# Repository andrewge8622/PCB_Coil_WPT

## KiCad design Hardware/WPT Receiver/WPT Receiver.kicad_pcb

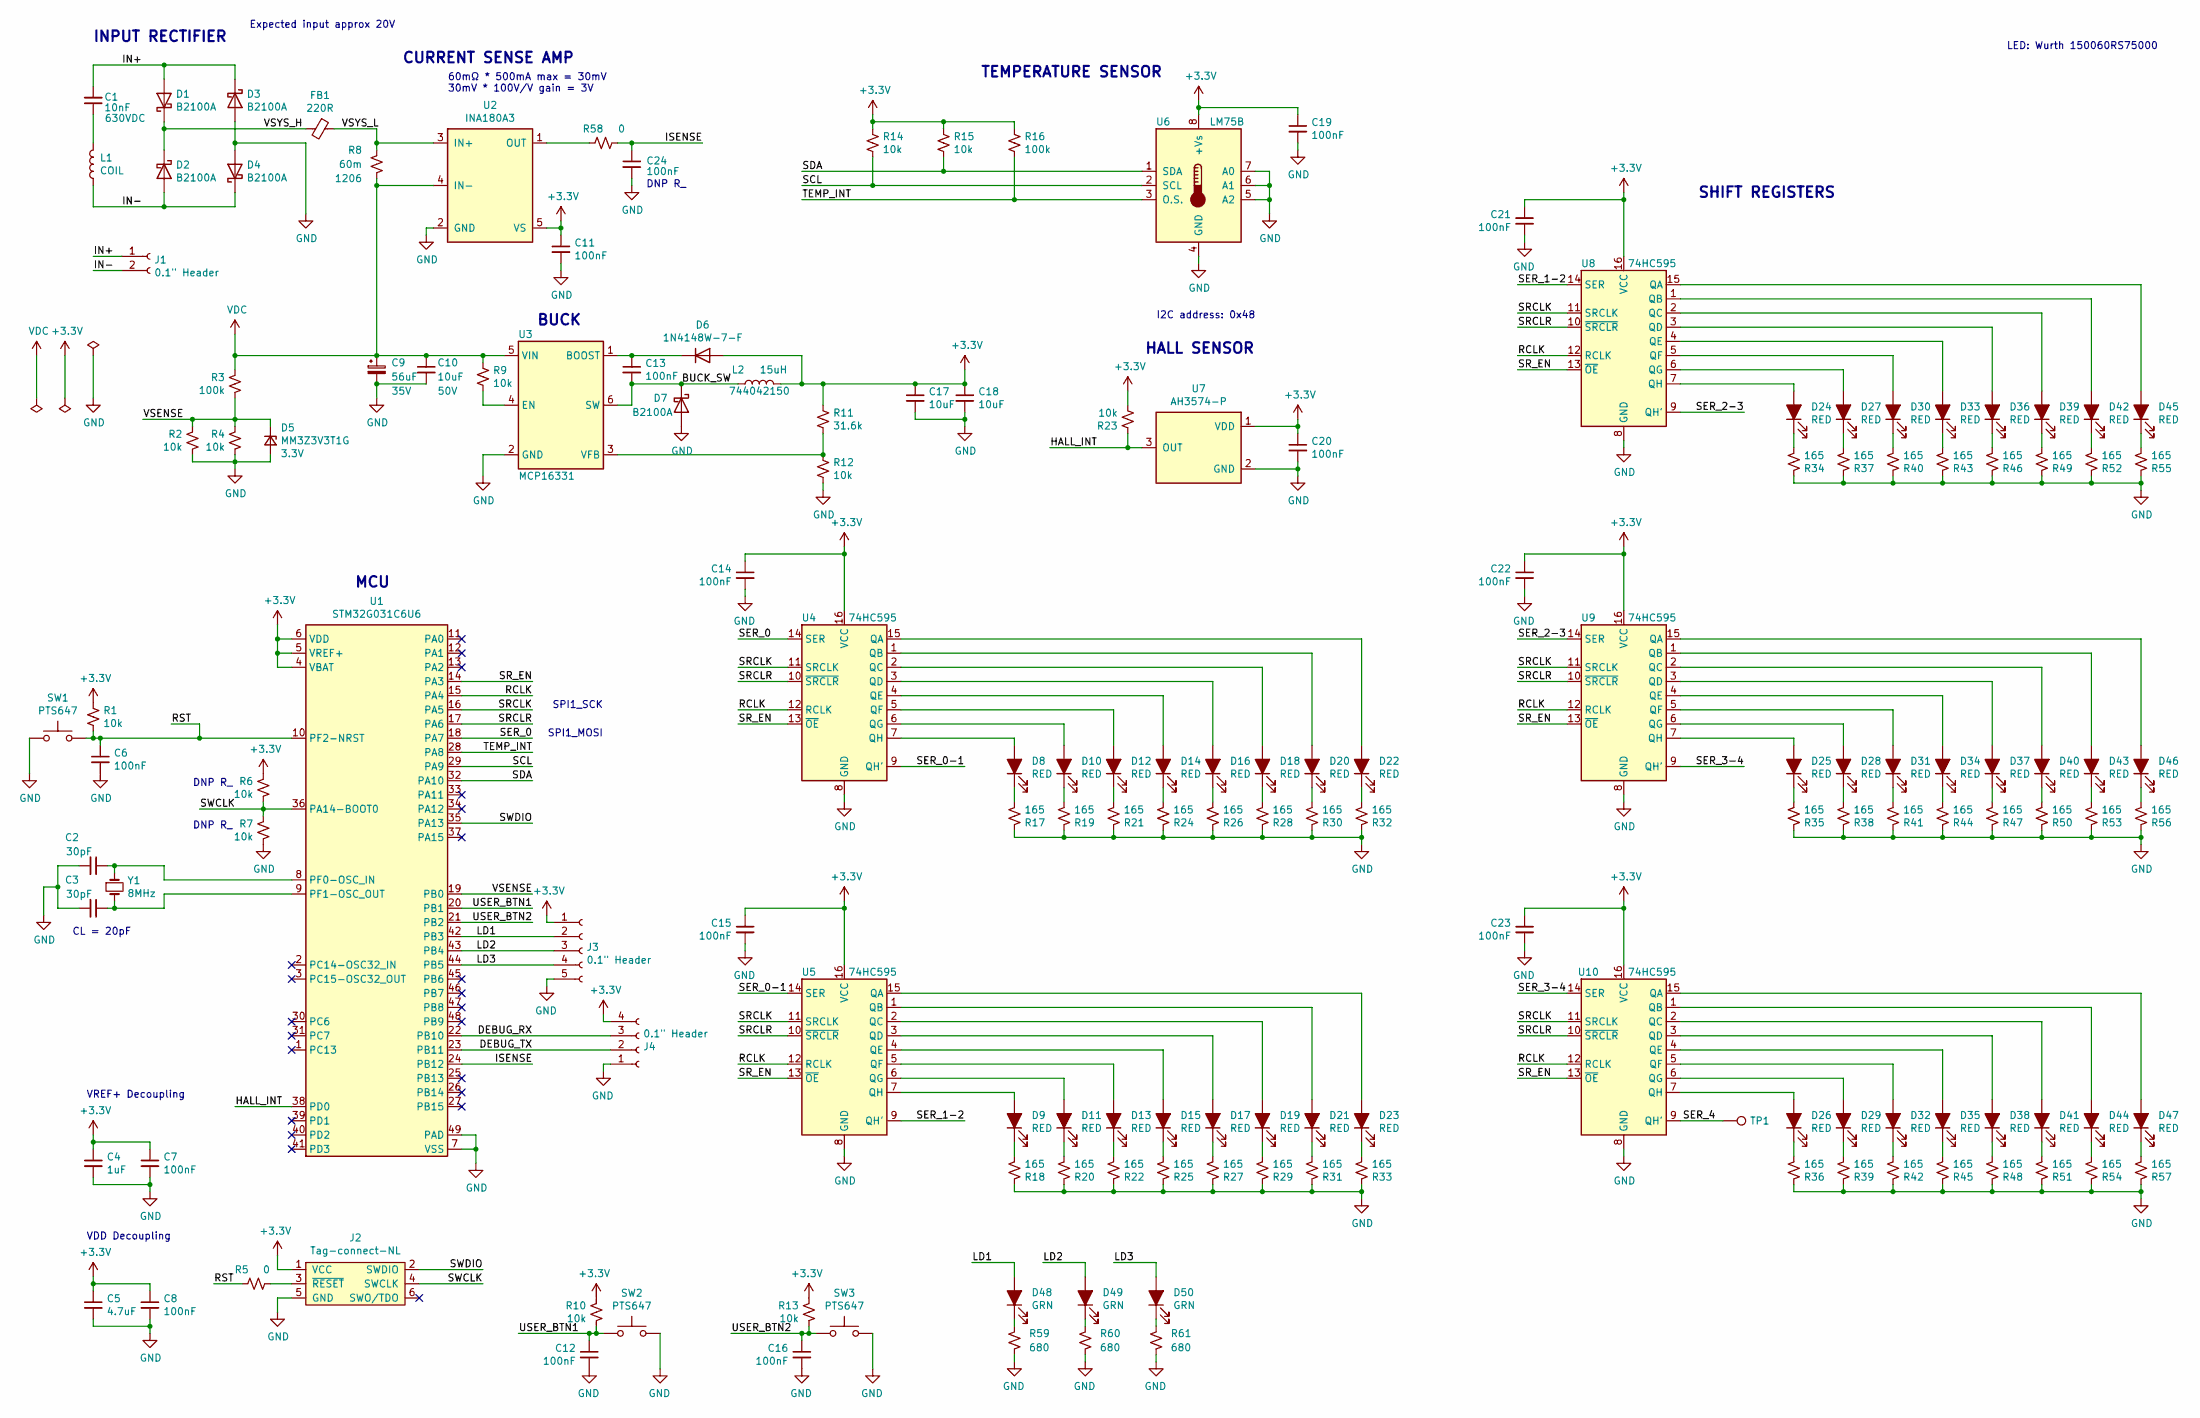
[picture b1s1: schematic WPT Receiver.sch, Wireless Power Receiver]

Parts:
C1: 10nF; C_Rect_L7.2mm_W8.5mm_P5.00mm_FKP2_FKP2_MKS2_MKP2; Voltage 630VDC
C2, C3: 30pF; C_0402_1005Metric
C4: 1uF; C_0603_1608Metric
C5: 4.7uF; C_0603_1608Metric
C6, C7, C8, C11, C12, C13, C14, C15, C16, C19, C20, C21, C22, C23, C24: 100nF; C_0402_1005Metric
C9: 56uF; CP_Elec_10x10; MPN EMVA630ADA560MJA0G
C10, C17, C18: 10uF; C_0603_1608Metric
D1, D2, D3, D4, D7: B2100A; D_SMA
D5: MM3Z3V3T1G; D_SOD-323; Voltage 3.3V
D6: 1N4148W-7-F; D_SOD-123
D8, D9, D10, D11, D12, D13, D14, D15, D16, D17, D18, D19, D20, D21, D22, D23, D24, D25, D26, D27, D28, D29, D30, D31, D32, D33, D34, D35, D36, D37, D38, D39, D40, D41, D42, D43, D44, D45, D46, D47: RED; LED_0603_1608Metric_Castellated
D48, D49, D50: GRN; LED_0603_1608Metric_Castellated; MPN 150060VS75000
FB1: 220R; L_0603_1608Metric
J1: 0.1\" Header; PinHeader_1x02_P2.54mm_Vertical
J2: Tag-connect-NL; TC2030-IDC-NL-FP
J3: 0.1\" Header; PinHeader_1x05_P2.54mm_Vertical
J4: 0.1\" Header; PinHeader_1x04_P2.54mm_Vertical
L1: COIL; PinHeader_2x01_P2.54mm_Vertical
L2: 15uH; 744042150; MPN 744042150
R1, R2, R4, R6, R7, R9, R10, R12, R13, R14, R15, R23: 10k; R_0603_1608Metric
R3, R16: 100k; R_0603_1608Metric
R5, R58: 0; R_0603_1608Metric
R8: 60m; R_1206_3216Metric
R11: 31.6k; R_0603_1608Metric
R17, R18, R19, R20, R21, R22, R24, R25, R26, R27, R28, R29, R30, R31, R32, R33, R34, R35, R36, R37, R38, R39, R40, R41, R42, R43, R44, R45, R46, R47, R48, R49, R50, R51, R52, R53, R54, R55, R56, R57: 165; R_0603_1608Metric
R59, R60, R61: 680; R_0603_1608Metric
SW1, SW2, SW3: PTS647
TP1: TestPoint; TestPoint_Pad_2.5x2.5mm
U1: STM32G031C6U6; QFN-48-1EP_7x7mm_P0.5mm_EP5.6x5.6mm
U2: INA180A3; SOT-23-5
U3: MCP16331; SOT-23-6
U4, U5, U8, U9, U10: 74HC595; SOIC-16_3.9x9.9mm_P1.27mm
U6: LM75B; SOIC-8_3.9x4.9mm_P1.27mm
U7: AH3574-P; TO-92Flat
Y1: 8MHz; Crystal_SMD_5032-2Pin_5.0x3.2mm

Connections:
+3V3: C4.1, C5.1, C7.1, C8.1, C11.1, C14.1, C15.1, C17.1, C18.1, C19.1, C20.1, C21.1, C22.1, C23.1, D6.2 (A), J2.1 (VCC), J3.1, J4.4, L2.2, R1.1, R6.2, R10.1, R11.1, R13.1, R14.1, R15.1, R16.1, R23.2, U1.4 (VBAT), U1.5 (VREF+), U1.6 (VDD), U2.5 (VS), U4.16 (VCC), U5.16 (VCC), U6.8 (+Vs), U7.1 (VDD), U8.16 (VCC), U9.16 (VCC), U10.16 (VCC)
/BUCK_SW: C13.2, D7.1 (K), L2.1, U3.6 (SW)
/DEBUG_RX: J4.3, U1.22 (PB10)
/DEBUG_TX: J4.2, U1.23 (PB11)
/HALL_INT: R23.1, U1.38 (PD0), U7.3 (OUT)
/IN+: C1.2, D1.2 (A), D3.1 (K), J1.1
/IN-: D2.2 (A), D4.1 (K), J1.2, L1.1
/ISENSE: C24.1, R58.1, U1.24 (PB12)
/LD1: D48.2 (A), J3.2, U1.42 (PB3)
/LD2: D49.2 (A), J3.3, U1.43 (PB4)
/LD3: D50.2 (A), J3.4, U1.44 (PB5)
/RCLK: U1.15 (PA4), U4.12 (RCLK), U5.12 (RCLK), U8.12 (RCLK), U9.12 (RCLK), U10.12 (RCLK)
/RST: C6.1, R1.2, R5.1, SW1.2, U1.10 (PF2-NRST)
/SCL: R14.2, U1.29 (PA9), U6.2 (SCL)
/SDA: R15.2, U1.32 (PA10), U6.1 (SDA)
/SER_0: U1.18 (PA7), U4.14 (SER)
/SER_0-1: U4.9 (QH'), U5.14 (SER)
/SER_1-2: U5.9 (QH'), U8.14 (SER)
/SER_2-3: U8.9 (QH'), U9.14 (SER)
/SER_3-4: U9.9 (QH'), U10.14 (SER)
/SER_4: TP1.1, U10.9 (QH')
/SRCLK: U1.16 (PA5), U4.11 (SRCLK), U5.11 (SRCLK), U8.11 (SRCLK), U9.11 (SRCLK), U10.11 (SRCLK)
/SRCLR: U1.17 (PA6), U4.10 (~SRCLR), U5.10 (~SRCLR), U8.10 (~SRCLR), U9.10 (~SRCLR), U10.10 (~SRCLR)
/SR_EN: U1.14 (PA3), U4.13 (~OE), U5.13 (~OE), U8.13 (~OE), U9.13 (~OE), U10.13 (~OE)
/SWCLK: J2.4 (SWCLK), R6.1, R7.2, U1.36 (PA14-BOOT0)
/SWDIO: J2.2 (SWDIO), U1.35 (PA13)
/TEMP_INT: R16.2, U1.28 (PA8), U6.3 (O.S.)
/USER_BTN1: C12.1, R10.2, SW2.2, U1.20 (PB1)
/USER_BTN2: C16.1, R13.2, SW3.2, U1.21 (PB2)
/VSENSE: D5.1 (K), R2.1, R3.2, R4.1, U1.19 (PB0)
/VSYS_H: D1.1 (K), D2.1 (K), FB1.2
/VSYS_L: FB1.1, R8.1, U2.3 (IN+)
GND: C2.2, C3.2, C4.2, C5.2, C6.2, C7.2, C8.2, C9.2, C10.2, C11.2, C12.2, C14.2, C15.2, C16.2, C17.2, C18.2, C19.2, C20.2, C21.2, C22.2, C23.2, C24.2, D3.2 (A), D4.2 (A), D5.2 (A), D7.2 (A), J2.5 (GND), J3.5, J4.1, R2.2, R4.2, R7.1, R12.2, R17.2, R18.2, R19.2, R20.2, R21.2, R22.2, R24.2, R25.2, R26.2, R27.2, R28.2, R29.2, R30.2, R31.2, R32.2, R33.2, R34.2, R35.2, R36.2, R37.2, R38.2, R39.2, R40.2, R41.2, R42.2, R43.2, R44.2, R45.2, R46.2, R47.2, R48.2, R49.2, R50.2, R51.2, R52.2, R53.2, R54.2, R55.2, R56.2, R57.2, R59.2, R60.2, R61.2, SW1.1, SW2.1, SW3.1, U1.7 (VSS), U1.49 (PAD), U2.2 (GND), U3.2 (GND), U4.8 (GND), U5.8 (GND), U6.4 (GND), U6.5 (A2), U6.6 (A1), U6.7 (A0), U7.2 (GND), U8.8 (GND), U9.8 (GND), U10.8 (GND)
unnamed: C1.1, L1.2
unnamed: C2.1, U1.8 (PF0-OSC_IN), Y1.1
unnamed: C3.1, U1.9 (PF1-OSC_OUT), Y1.2
unnamed: C13.1, D6.1 (K), U3.1 (BOOST)
unnamed: D8.1 (K), R17.1
unnamed: D8.2 (A), U4.7 (QH)
unnamed: D9.1 (K), R18.1
unnamed: D9.2 (A), U5.7 (QH)
unnamed: D10.1 (K), R19.1
unnamed: D10.2 (A), U4.6 (QG)
unnamed: D11.1 (K), R20.1
unnamed: D11.2 (A), U5.6 (QG)
unnamed: D12.1 (K), R21.1
unnamed: D12.2 (A), U4.5 (QF)
unnamed: D13.1 (K), R22.1
unnamed: D13.2 (A), U5.5 (QF)
unnamed: D14.1 (K), R24.1
unnamed: D14.2 (A), U4.4 (QE)
unnamed: D15.1 (K), R25.1
unnamed: D15.2 (A), U5.4 (QE)
unnamed: D16.1 (K), R26.1
unnamed: D16.2 (A), U4.3 (QD)
unnamed: D17.1 (K), R27.1
unnamed: D17.2 (A), U5.3 (QD)
unnamed: D18.1 (K), R28.1
unnamed: D18.2 (A), U4.2 (QC)
unnamed: D19.1 (K), R29.1
unnamed: D19.2 (A), U5.2 (QC)
unnamed: D20.1 (K), R30.1
unnamed: D20.2 (A), U4.1 (QB)
unnamed: D21.1 (K), R31.1
unnamed: D21.2 (A), U5.1 (QB)
unnamed: D22.1 (K), R32.1
unnamed: D22.2 (A), U4.15 (QA)
unnamed: D23.1 (K), R33.1
unnamed: D23.2 (A), U5.15 (QA)
unnamed: D24.1 (K), R34.1
unnamed: D24.2 (A), U8.7 (QH)
unnamed: D25.1 (K), R35.1
unnamed: D25.2 (A), U9.7 (QH)
unnamed: D26.1 (K), R36.1
unnamed: D26.2 (A), U10.7 (QH)
unnamed: D27.1 (K), R37.1
unnamed: D27.2 (A), U8.6 (QG)
unnamed: D28.1 (K), R38.1
unnamed: D28.2 (A), U9.6 (QG)
unnamed: D29.1 (K), R39.1
unnamed: D29.2 (A), U10.6 (QG)
unnamed: D30.1 (K), R40.1
unnamed: D30.2 (A), U8.5 (QF)
unnamed: D31.1 (K), R41.1
unnamed: D31.2 (A), U9.5 (QF)
unnamed: D32.1 (K), R42.1
unnamed: D32.2 (A), U10.5 (QF)
unnamed: D33.1 (K), R43.1
unnamed: D33.2 (A), U8.4 (QE)
unnamed: D34.1 (K), R44.1
unnamed: D34.2 (A), U9.4 (QE)
unnamed: D35.1 (K), R45.1
unnamed: D35.2 (A), U10.4 (QE)
unnamed: D36.1 (K), R46.1
unnamed: D36.2 (A), U8.3 (QD)
unnamed: D37.1 (K), R47.1
unnamed: D37.2 (A), U9.3 (QD)
unnamed: D38.1 (K), R48.1
unnamed: D38.2 (A), U10.3 (QD)
unnamed: D39.1 (K), R49.1
unnamed: D39.2 (A), U8.2 (QC)
unnamed: D40.1 (K), R50.1
unnamed: D40.2 (A), U9.2 (QC)
unnamed: D41.1 (K), R51.1
unnamed: D41.2 (A), U10.2 (QC)
unnamed: D42.1 (K), R52.1
unnamed: D42.2 (A), U8.1 (QB)
unnamed: D43.1 (K), R53.1
unnamed: D43.2 (A), U9.1 (QB)
unnamed: D44.1 (K), R54.1
unnamed: D44.2 (A), U10.1 (QB)
unnamed: D45.1 (K), R55.1
unnamed: D45.2 (A), U8.15 (QA)
unnamed: D46.1 (K), R56.1
unnamed: D46.2 (A), U9.15 (QA)
unnamed: D47.1 (K), R57.1
unnamed: D47.2 (A), U10.15 (QA)
unnamed: D48.1 (K), R59.1
unnamed: D49.1 (K), R60.1
unnamed: D50.1 (K), R61.1
unnamed: J2.3 (~RESET), R5.2
unnamed: R9.2, U3.4 (EN)
unnamed: R11.2, R12.1, U3.3 (VFB)
unnamed: R58.2, U2.1 (OUT)
VDC: C9.1, C10.1, R3.1, R8.2, R9.1, U2.4 (IN-), U3.5 (VIN)

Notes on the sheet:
DNP R_
VDD Decoupling
VREF+ Decoupling
Expected input approx 20V
CL = 20pF
60mΩ * 500mA max = 30mV 30mV * 100V/V gain = 3V
I2C address: 0x48
SPI1_SCK
SPI1_MOSI
LED: Wurth 150060RS75000
HALL SENSOR
TEMPERATURE SENSOR
INPUT RECTIFIER
CURRENT SENSE AMP
BUCK
MCU
SHIFT REGISTERS

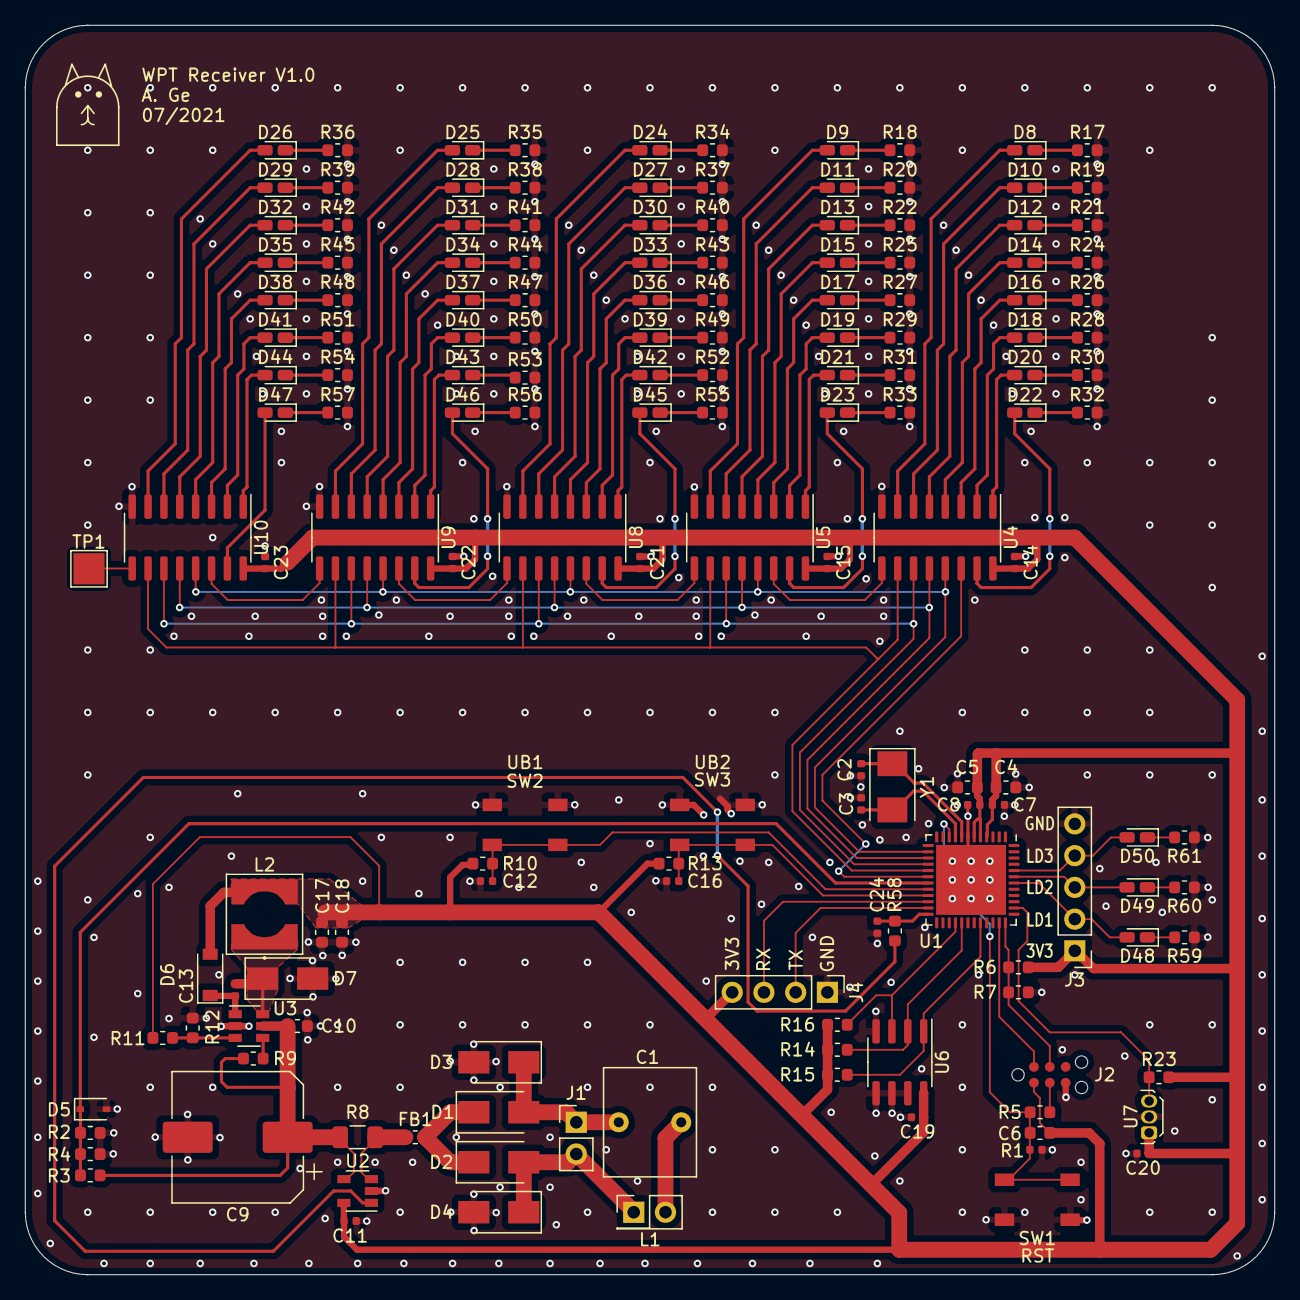
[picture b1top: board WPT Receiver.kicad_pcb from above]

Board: 2 copper layers, 100.0 x 100.0 mm, 157 parts (0 on the bottom side), 125 nets.

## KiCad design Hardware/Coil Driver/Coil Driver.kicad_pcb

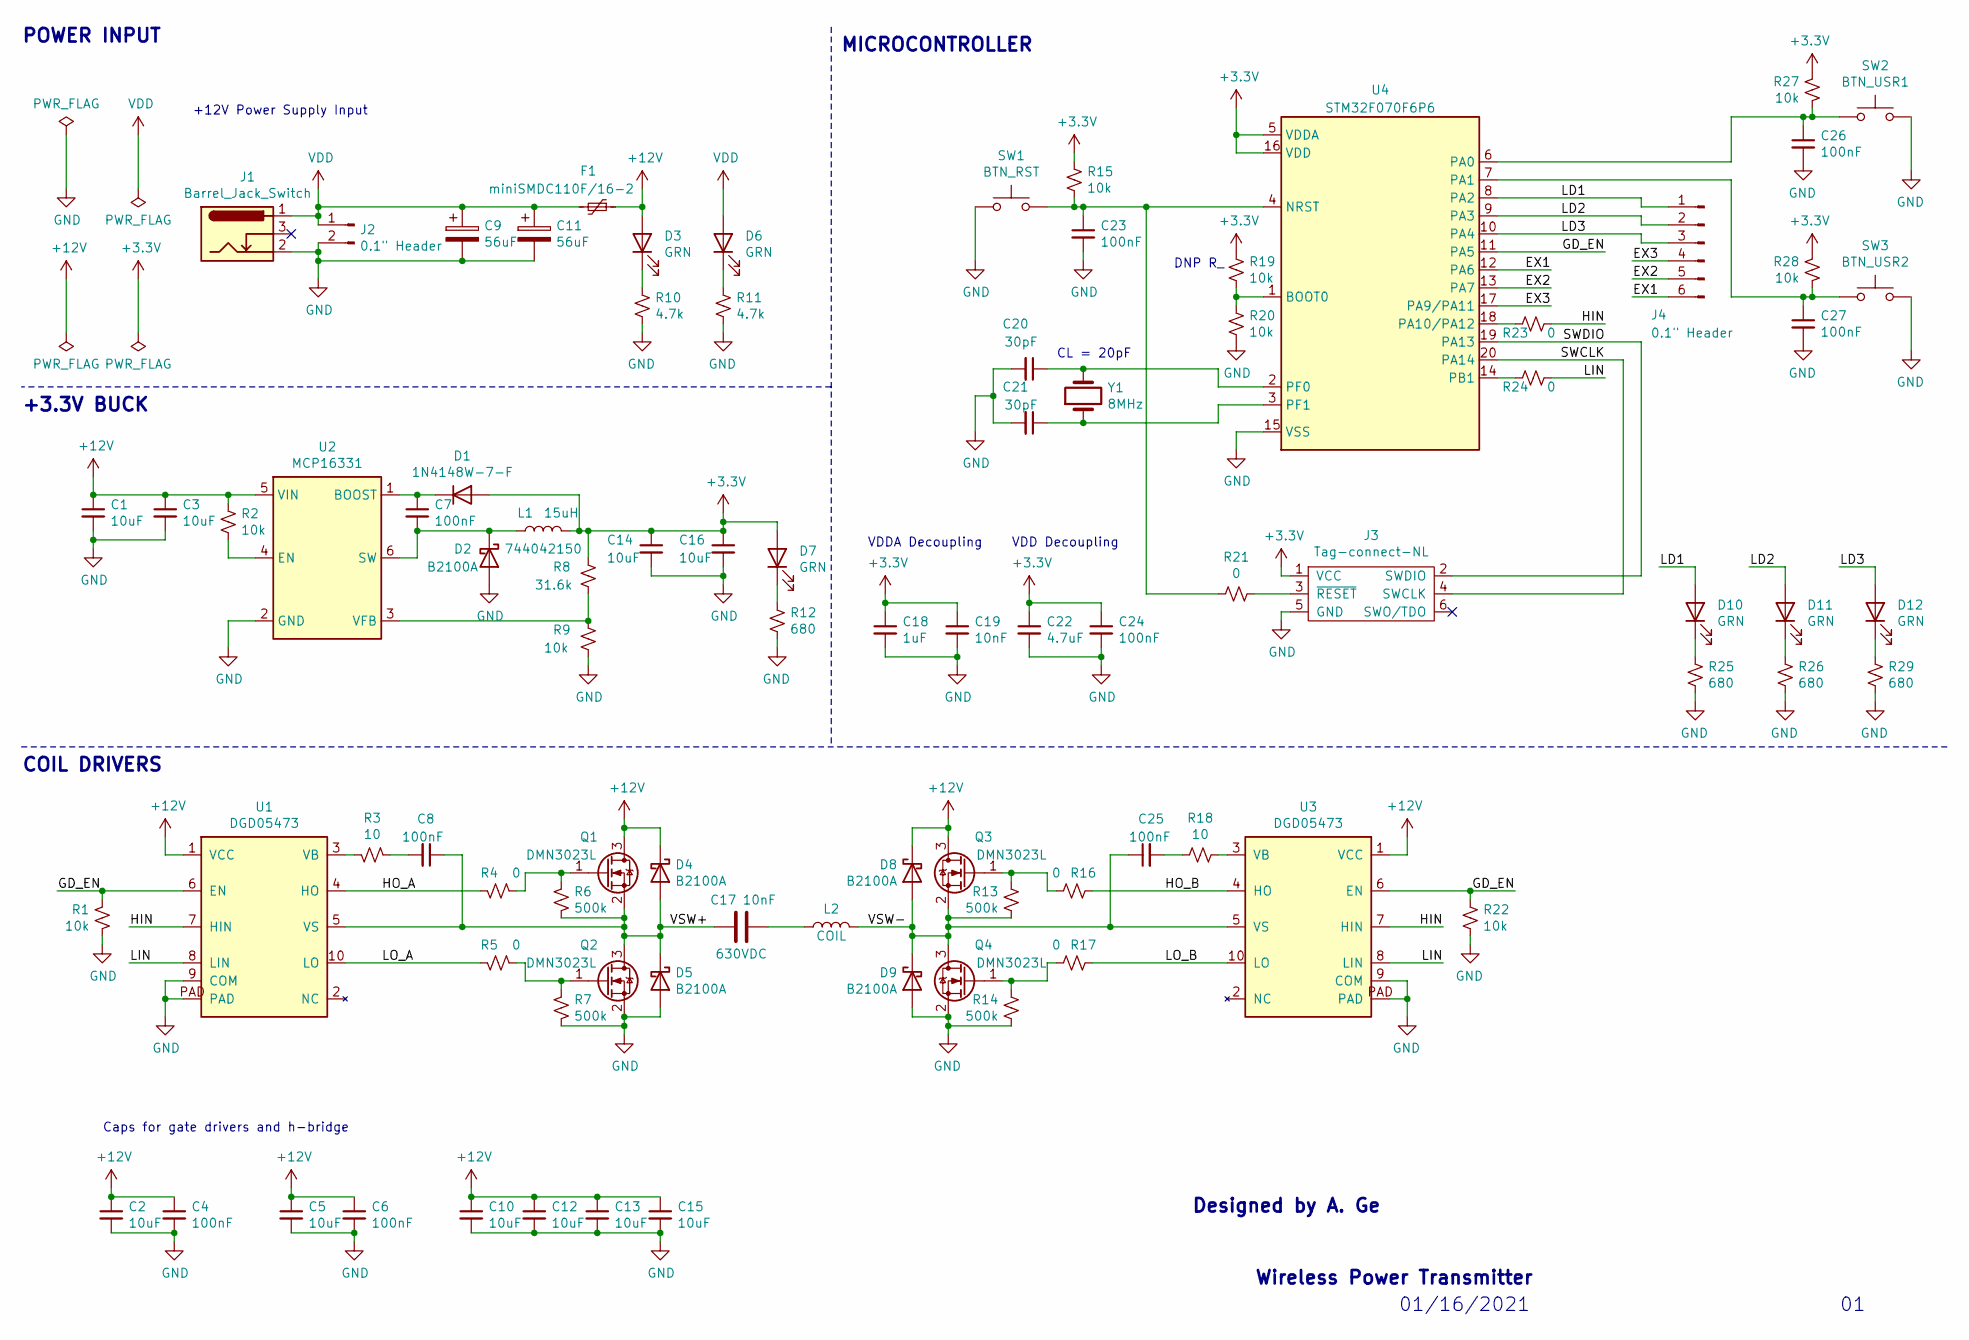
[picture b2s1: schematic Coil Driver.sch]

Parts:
C1, C2, C3, C5, C10, C12, C13, C14, C15, C16: 10uF; C_0603_1608Metric
C4, C6, C7, C8, C23, C24, C25, C26, C27: 100nF; C_0402_1005Metric
C9, C11: 56uF; CP_Elec_6.3x7.7
C17: 10nF; C_Rect_L7.2mm_W8.5mm_P5.00mm_FKP2_FKP2_MKS2_MKP2; Voltage Rating 630VDC; MPN FKP2J021001L00JSC9
C18: 1uF; C_0603_1608Metric
C19: 10nF; C_0402_1005Metric
C20, C21: 30pF; C_0402_1005Metric
C22: 4.7uF; C_0603_1608Metric
D1: 1N4148W-7-F; D_SOD-123
D2, D4, D5, D8, D9: B2100A; D_SMA
D3, D6, D7, D10, D11, D12: GRN; LED_0603_1608Metric; MPN 150060VS75000
F1: miniSMDC110F/16-2; miniSMDC110F_16-2
J1: Barrel_Jack_Switch; BarrelJack_CUI_PJ-102AH_Horizontal
J2: 0.1\" Header; PinHeader_1x02_P2.54mm_Vertical
J3: Tag-connect-NL; TC2030-IDC-NL-FP
J4: 0.1\" Header; PinHeader_1x06_P2.54mm_Vertical
L1: 15uH; 744042150; MPN 744042150
L2: COIL; PinSocket_1x02_P2.54mm_Vertical
Q1, Q2, Q3, Q4: DMN3023L; SOT-23
R1, R2, R9, R15, R19, R20, R22, R27, R28: 10k; R_0603_1608Metric
R3, R18: 10; R_0805_2012Metric
R4, R5, R16, R17, R21, R23, R24: 0; R_0603_1608Metric
R6, R7, R13, R14: 500k; R_0603_1608Metric
R8: 31.6k; R_0603_1608Metric
R10, R11: 4.7k; R_0603_1608Metric
R12, R25, R26, R29: 680; R_0603_1608Metric
SW1: BTN_RST; PTS647
SW2: BTN_USR1; PTS647
SW3: BTN_USR2; PTS647
U1, U3: DGD05473; W-DFN3030-10
U2: MCP16331; SOT-23-6
U4: STM32F070F6P6; TSSOP-20_4.4x6.5mm_P0.65mm
Y1: 8MHz; Crystal_SMD_5032-2Pin_5.0x3.2mm

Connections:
+3V3: C14.1, C16.1, C18.1, C19.1, C22.1, C24.1, D1.2 (A), D7.2 (A), J3.1 (VCC), L1.2, R8.1, R15.1, R19.1, R27.1, R28.1, U4.5 (VDDA), U4.16 (VDD)
+12V: C1.1, C2.1, C3.1, C4.1, C5.1, C6.1, C10.1, C12.1, C13.1, C15.1, D3.2 (A), D4.1 (K), D8.1 (K), F1.1, Q1.3 (D), Q3.3 (D), R2.1, U1.1 (VCC), U2.5 (VIN), U3.1 (VCC)
/EX1: J4.6, U4.12 (PA6)
/EX2: J4.5, U4.13 (PA7)
/EX3: J4.4, U4.17 (PA9/PA11)
/GD_EN: R1.2, R22.2, U1.6 (EN), U3.6 (EN), U4.11 (PA5)
/HIN: R23.1, U1.7 (HIN), U3.7 (HIN)
/HO_A: R4.1, U1.4 (HO)
/HO_B: R16.1, U3.4 (HO)
/LD1: D10.2 (A), J4.1, U4.8 (PA2)
/LD2: D11.2 (A), J4.2, U4.9 (PA3)
/LD3: D12.2 (A), J4.3, U4.10 (PA4)
/LIN: R24.1, U1.8 (LIN), U3.8 (LIN)
/LO_A: R5.1, U1.10 (LO)
/LO_B: R17.1, U3.10 (LO)
/SWCLK: J3.4 (SWCLK), U4.20 (PA14)
/SWDIO: J3.2 (SWDIO), U4.19 (PA13)
/VSW+: C8.1, C17.2, D4.2 (A), D5.1 (K), Q1.2 (S), Q2.3 (D), R6.2, U1.5 (VS)
/VSW-: C25.1, D8.2 (A), D9.1 (K), L2.2, Q3.2 (S), Q4.3 (D), R13.2, U3.5 (VS)
GND: C1.2, C2.2, C3.2, C4.2, C5.2, C6.2, C9.2, C10.2, C11.2, C12.2, C13.2, C14.2, C15.2, C16.2, C18.2, C19.2, C20.2, C21.2, C22.2, C23.2, C24.2, C26.2, C27.2, D2.2 (A), D5.2 (A), D9.2 (A), J1.2, J2.2, J3.5 (GND), Q2.2 (S), Q4.2 (S), R1.1, R7.2, R9.2, R10.2, R11.2, R12.2, R14.2, R20.2, R22.1, R25.2, R26.2, R29.2, SW1.1, SW2.1, SW3.1, U1.9 (COM), U1.PAD, U2.2 (GND), U3.9 (COM), U3.PAD, U4.15 (VSS)
unnamed: C7.1, D1.1 (K), U2.1 (BOOST)
unnamed: C7.2, D2.1 (K), L1.1, U2.6 (SW)
unnamed: C8.2, R3.2
unnamed: C17.1, L2.1
unnamed: C20.1, U4.2 (PF0), Y1.2
unnamed: C21.1, U4.3 (PF1), Y1.1
unnamed: C23.1, R15.2, R21.2, SW1.2, U4.4 (NRST)
unnamed: C25.2, R18.2
unnamed: C26.1, R27.2, SW2.2, U4.6 (PA0)
unnamed: C27.1, R28.2, SW3.2, U4.7 (PA1)
unnamed: D3.1 (K), R10.1
unnamed: D6.1 (K), R11.1
unnamed: D7.1 (K), R12.1
unnamed: D10.1 (K), R25.1
unnamed: D11.1 (K), R26.1
unnamed: D12.1 (K), R29.1
unnamed: J3.3 (~RESET), R21.1
unnamed: Q1.1 (G), R4.2, R6.1
unnamed: Q2.1 (G), R5.2, R7.1
unnamed: Q3.1 (G), R13.1, R16.2
unnamed: Q4.1 (G), R14.1, R17.2
unnamed: R2.2, U2.4 (EN)
unnamed: R3.1, U1.3 (VB)
unnamed: R8.2, R9.1, U2.3 (VFB)
unnamed: R18.1, U3.3 (VB)
unnamed: R19.2, R20.1, U4.1 (BOOT0)
unnamed: R23.2, U4.18 (PA10/PA12)
unnamed: R24.2, U4.14 (PB1)
VDD: C9.1, C11.1, D6.2 (A), F1.2, J1.1, J2.1

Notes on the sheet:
Caps for gate drivers and h-bridge
DNP R_
VDDA Decoupling
VDD Decoupling
+12V Power Supply Input
Designed by A. Ge
Wireless Power Transmitter
01/16/2021
MICROCONTROLLER
POWER INPUT
+3.3V BUCK
COIL DRIVERS
CL = 20pF

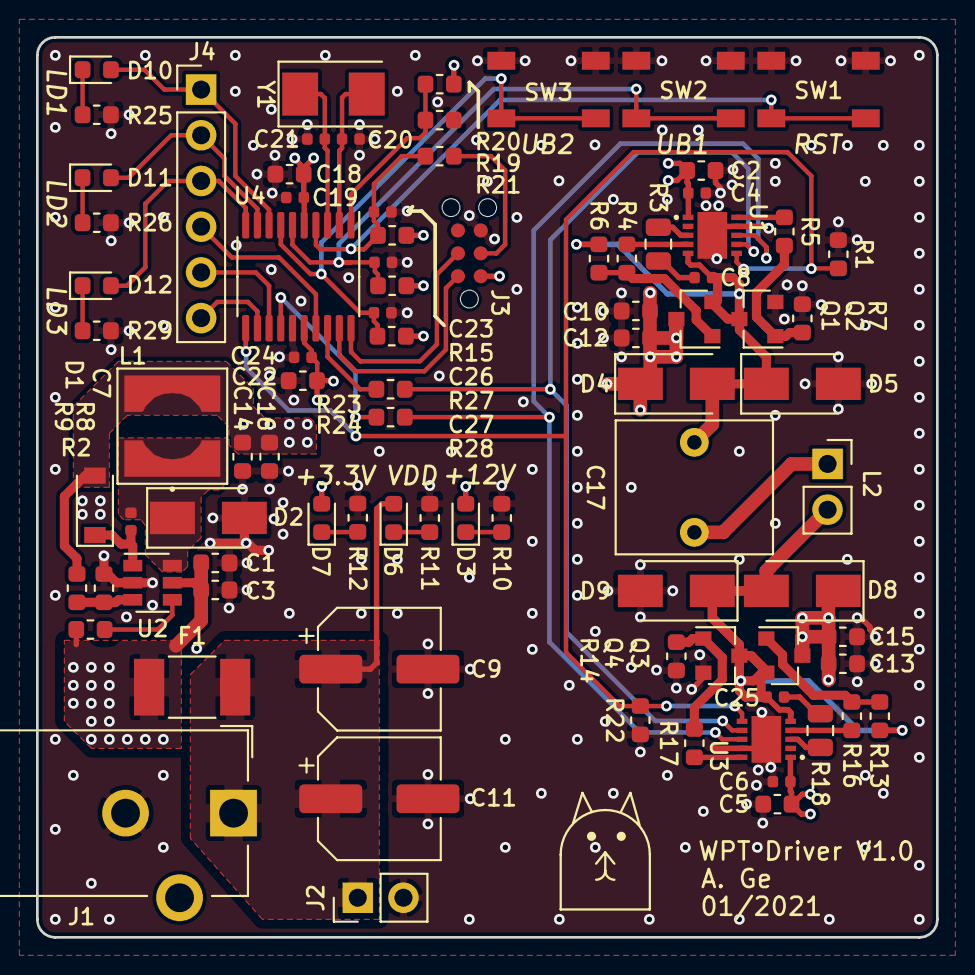
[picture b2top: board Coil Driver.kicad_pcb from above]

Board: 4 copper layers, 50.0 x 50.0 mm, 87 parts (0 on the bottom side), 49 nets.

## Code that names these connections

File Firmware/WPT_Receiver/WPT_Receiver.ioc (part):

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Mcu.Name=STM32G031C(4-6-8)Ux
Mcu.Package=UFQFPN48
Mcu.UserName=STM32G031C6Ux
PA10.Mode=I2C
PA10.Signal=I2C1_SDA
PA13.Mode=Serial_Wire
PA13.Signal=SYS_SWDIO
PA14-BOOT0.Mode=Serial_Wire
PA14-BOOT0.Signal=SYS_SWCLK
PA3.GPIOParameters=GPIO_Label
PA3.GPIO_Label=SR_EN
PA3.Signal=S_TIM2_CH4
PA4.GPIOParameters=GPIO_Label
PA4.GPIO_Label=RCLK
PA4.Signal=GPIO_Output
PA5.GPIOParameters=GPIO_Label
PA5.GPIO_Label=SRCLK
PA5.Mode=TX_Only_Simplex_Unidirect_Master
PA5.Signal=SPI1_SCK
PA6.GPIOParameters=GPIO_Label
PA6.GPIO_Label=SR_CLR
PA6.Signal=GPIO_Output
PA7.GPIOParameters=GPIO_Label
PA7.GPIO_Label=SER_O
PA7.Mode=TX_Only_Simplex_Unidirect_Master
PA7.Signal=SPI1_MOSI
PA8.Signal=GPXTI8
PA9.Mode=I2C
PA9.Signal=I2C1_SCL
PB0.GPIOParameters=GPIO_Label
PB0.GPIO_Label=VSENSE
PB0.Mode=IN8
PB0.Signal=ADC1_IN8
PB1.GPIOParameters=GPIO_Label,GPIO_ModeDefaultEXTI
PB1.GPIO_Label=USER_BTN_1
PB1.GPIO_ModeDefaultEXTI=GPIO_MODE_IT_FALLING
PB1.Signal=GPXTI1
PB10.Mode=Asynchronous
PB10.Signal=LPUART1_RX
PB11.Mode=Asynchronous
PB11.Signal=LPUART1_TX
PB12.GPIOParameters=GPIO_Label
PB12.GPIO_Label=ISENSE
PB12.Mode=IN16
PB12.Signal=ADC1_IN16
PB2.GPIOParameters=GPIO_Label,GPIO_ModeDefaultEXTI
PB2.GPIO_Label=USER_BTN_2
PB2.GPIO_ModeDefaultEXTI=GPIO_MODE_IT_FALLING
PB2.Signal=GPXTI2
PB3.GPIOParameters=GPIO_Label
PB3.GPIO_Label=LD1
PB3.Signal=GPIO_Output
PB4.GPIOParameters=GPIO_Label
PB4.GPIO_Label=LD2
PB4.Signal=GPIO_Output
PB5.GPIOParameters=GPIO_Label
PB5.GPIO_Label=LD3
PB5.Signal=GPIO_Output
PD0.GPIOParameters=GPIO_Label,GPIO_ModeDefaultEXTI
PD0.GPIO_Label=HALL_INT
PD0.GPIO_ModeDefaultEXTI=GPIO_MODE_IT_RISING_FALLING
PD0.Signal=GPXTI0
PF0-OSC_IN\ (PF0).Mode=HSE-External-Oscillator
PF0-OSC_IN\ (PF0).Signal=RCC_OSC_IN
PF1-OSC_OUT\ (PF1).Mode=HSE-External-Oscillator
PF1-OSC_OUT\ (PF1).Signal=RCC_OSC_OUT
RCC.HSE_VALUE=8000000
RCC.SYSCLKFreq_VALUE=8000000
RCC.SYSCLKSource=RCC_SYSCLKSOURCE_HSE
board=custom

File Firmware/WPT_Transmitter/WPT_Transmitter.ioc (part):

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Mcu.Name=STM32F070F6Px
Mcu.Package=TSSOP20
Mcu.UserName=STM32F070F6Px
PA0.GPIOParameters=GPIO_Label,GPIO_ModeDefaultEXTI
PA0.GPIO_Label=USR1
PA0.GPIO_ModeDefaultEXTI=GPIO_MODE_IT_FALLING
PA0.Signal=GPXTI0
PA1.GPIOParameters=GPIO_Label,GPIO_ModeDefaultEXTI
PA1.GPIO_Label=USR2
PA1.GPIO_ModeDefaultEXTI=GPIO_MODE_IT_FALLING
PA1.Signal=GPXTI1
PA10.GPIOParameters=GPIO_Label
PA10.GPIO_Label=HIN
PA10.Signal=S_TIM1_CH3
PA13.Mode=Serial_Wire
PA13.Signal=SYS_SWDIO
PA14.Mode=Serial_Wire
PA14.Signal=SYS_SWCLK
PA2.GPIOParameters=GPIO_Label
PA2.GPIO_Label=LD1
PA2.Signal=GPIO_Output
PA3.GPIOParameters=GPIO_Label
PA3.GPIO_Label=LD2
PA3.Signal=GPIO_Output
PA4.GPIOParameters=GPIO_Label
PA4.GPIO_Label=LD3
PA4.Signal=GPIO_Output
PA5.GPIOParameters=GPIO_Label
PA5.GPIO_Label=GD_EN
PA5.Signal=GPIO_Output
PA6.GPIOParameters=GPIO_Label
PA6.GPIO_Label=EX1
PA6.Signal=GPIO_Input
PA7.GPIOParameters=GPIO_Label
PA7.GPIO_Label=EX2
PA7.Signal=GPIO_Input
PA9.GPIOParameters=GPIO_Label
PA9.GPIO_Label=EX3
PA9.Signal=GPIO_Input
PB1.GPIOParameters=GPIO_Label
PB1.GPIO_Label=LIN
PB1.Mode=PWM Generation3 CH3 CH3N
PB1.Signal=TIM1_CH3N
PF0-OSC_IN.Mode=HSE-External-Oscillator
PF0-OSC_IN.Signal=RCC_OSC_IN
PF1-OSC_OUT.Mode=HSE-External-Oscillator
PF1-OSC_OUT.Signal=RCC_OSC_OUT
RCC.SYSCLKFreq_VALUE=32000000
RCC.SYSCLKSource=RCC_SYSCLKSOURCE_PLLCLK
board=custom

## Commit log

2020-11-12 adding Kicad files
2020-11-12 added symbols for gate driver and schottky diode, footprint for gate driver
2020-11-12 added WIMA film cap for resonant tank. Symbol is not structured well, but this seems to be a limitation of Kicad
2020-11-20 added components for buck converter and boost diode
2020-11-20 Started schematic capture. Finished first draft of input, buck, and h-bridge. Modified symbols for cleaner schematic.
2020-11-21 moving .gitignore to hardware folder to prepare for committing firmware folder. Also modified decoupling caps for gate drivers
2020-11-21 Delete .gitignore
    Removing from top level after adding to hardware subfolder
2020-11-21 adding .gitignore file for keil project
2020-11-21 adding initially generated cubemx files (configured for complementary PWM on TIM1 CH3, with inserted deadtime)
2020-12-10 added micro and button to library, added microcontroller to schematic, added boxes and title block info, and annotated refdes
2020-12-10 added a couple of GPIO in cubeMX
2020-12-10 Added power flags, passing ERC
2020-12-10 added footprint for resettable fuse
2020-12-25 changed WIMA cap to be standard capacitor part with new parameters
2020-12-25 created footprint for inductor and added parameters to schematic. Added switch footprint. Added several missing STEP models. Note that updating all from library may reset paths and cause STEPs from K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
2020-12-25 imported footprints into PCB document. Added user LEDs and power indication LEDs to schematic.
2020-12-27 Swapped out 8MHz crystal for 2 pin instead of 4 pin. Initial part placement (except for gate drivers/h-bridge) loosely complete. Decided board will be 4 layers to make routing of power nets easier.
2021-01-02 completed first draft of part placement, and switching loop layout of gate drivers
2021-01-03 Added internal layers, routed power input and buck converter, and repositioned a few components. Defined PCB shape and moved to center of drawing template.
2021-01-03 Done with initial routing of microcontroller. Flipped order of extra IO exposed on header to ease routing. Added some power pours
2021-01-03 done with routing other than a few power/ground connections
2021-01-03 added ground vias
2021-01-03 Added 12V and 3.3V vias, full connectivity. Passes DRC.
2021-01-03 Positioned all designators and added logo library
2021-01-16 added ground stitching vias throughout board, and via fence around switching region. More or less ready to go.
2021-01-16 fixed DRCs caused by new vias. oops.
2021-01-16 added silkscreen label and rev
2021-05-22 committing final changes to coil driver, and creating new kicad folder for receiver
2021-05-22 created libraries that could be linked into new receiver project. Added STM32G031C6U6 and small Nexperia SOT323 FET to library
2021-05-22 Added input resonant tank, bridge rectifier, and buck to schematic for receiver
2021-05-22 updated title block parameters for both schematic. In receiver, modified symbol of STM32, added to schematic and also added crystal, decoupling caps, and buttons
2021-06-05 Added placeholder text for remaining parts of board (hall sensor, temp sensor, current sense, LEDs, etc.)
2021-06-05 started pin selection in CubeMX
2021-06-06 Created symbols for INA180 and Hall sensor. Added to schematic and implemented supporting circuitry. Added background color to old tag connect symbol
2021-06-06 Added most of pinout for STM32G0, as well as measurement circuit for voltage sense. Added implementation for one shift reg.
2021-06-06 Removed a bunch of ground vias (especially stitching around switching area) that were causing discontinuity in 12V pour in power layer
2021-06-09 added and wired up shift registers, added debug headers, and modified pinout slightly. Cleaned up ERC and added power flags. Design passes ERC, ready to assign footprints
2021-06-09 small modifications to pinout
2021-07-22 Added footprint associations, as well as a few MPN/VDC parameters and an RC filter footprint on current sense line. Imported footprints into pcb
2021-07-22 Added an MPN to electrolytic caps in coil driver. Added debug LEDs to 3 pins on receiver micro
2021-07-23 started very rough part placement. Rounded board outline edges.
2021-07-27 Positioned non-power components, and routed most signals for peripherals other than shift regs/drivers. Added folder for 3D models for switch and crystal
2021-07-27 Changed some pinouts to ease routing, updated in Cube
2021-07-27 Routed all signals for shift regs and LEDs.
2021-07-30 Added routing for power input region (including buck) and a few other remaining signals. All signals now routed other than ground
2021-07-30 added ground vias for all signals, and ground pour on bottom layer
2021-07-30 Added tons of ground vias for stiching and to better connect islands. Added logo library and added to board
2021-07-31 Added silkscreen labels to headers, positioned all designators. First draft complete
2021-07-31 Fixed DRC errors. Added some silkscreen and generated gerbers and drill file
2021-07-31 small change to soldermask
2021-07-31 Copied in old inductor coil files and made updates for this round of testing. Generated Gerbers for all boards.
2021-09-29 Generated initial files using CubeMX and imported into Keil. Added a blinky, and also configured shift reg OE to high to avoid floating outputs
2021-09-29 Added code to read user buttons using interrupts, and toggle LEDs
2021-09-29 Added global static variable for which pin is showing blinky. Added logic within interrupt callback to increment/decrement pin based on button inputs
2021-10-01 Updated settings in cube. Wrote new interrupt routine (both rising and falling) for hall sensor output to enable LD3 when magnet present. Removed moving blinky, and instead made UB1 enable/disable bl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
2021-10-06 modified IOC file to enable DMA interrupts on IDLE (for LPUART1). Implemented variable length input on UART RX using DMA IDLE signal. Added function to reverse and echo received data to prove receive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
2021-10-14 Wrote header file and began implementing functions for SN74HC595 shift registers. Tested init function and verified (in main) that shift registers can be written to and controlled
2021-10-14 Modified Cube settings to enable timer2, channel4 as PWM output on SR_EN pin, for dimming of LEDs. Implemented enable/disable/PWM functions, modified init function, and got ClearAll function mostly w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
2021-10-14 modified some function definitions/declarations to sync between header and source files
2021-10-15 finished implementing and testing shift register functions. Added a TestReel function that demos all module functions
2021-10-15 started implementing ADC function. Transferring VSENSE channel to terminal over UART appears to work fine using sprintf.
2021-10-19 Updated pins, including labels, in Cube to match schematic. Wrote blinky to verify board MCU is operating. Note that boot resistor silkscreen labels were swapped, so MCU did not start up properly unt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
2021-10-19 Modified Cube settings again to enable interrupts on user buttons. Wrote interrupt callback so that user buttons can be used to turn on/off an LED, which will shortly be modified to control GD_EN pin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
